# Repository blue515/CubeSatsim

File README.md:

# CubeSatsim
**工作日誌**
https://1drv.ms/w/s!AnrOlf2GZ1a5vx4cTZ3XmwS1Cqu2?e=tUu3Cf

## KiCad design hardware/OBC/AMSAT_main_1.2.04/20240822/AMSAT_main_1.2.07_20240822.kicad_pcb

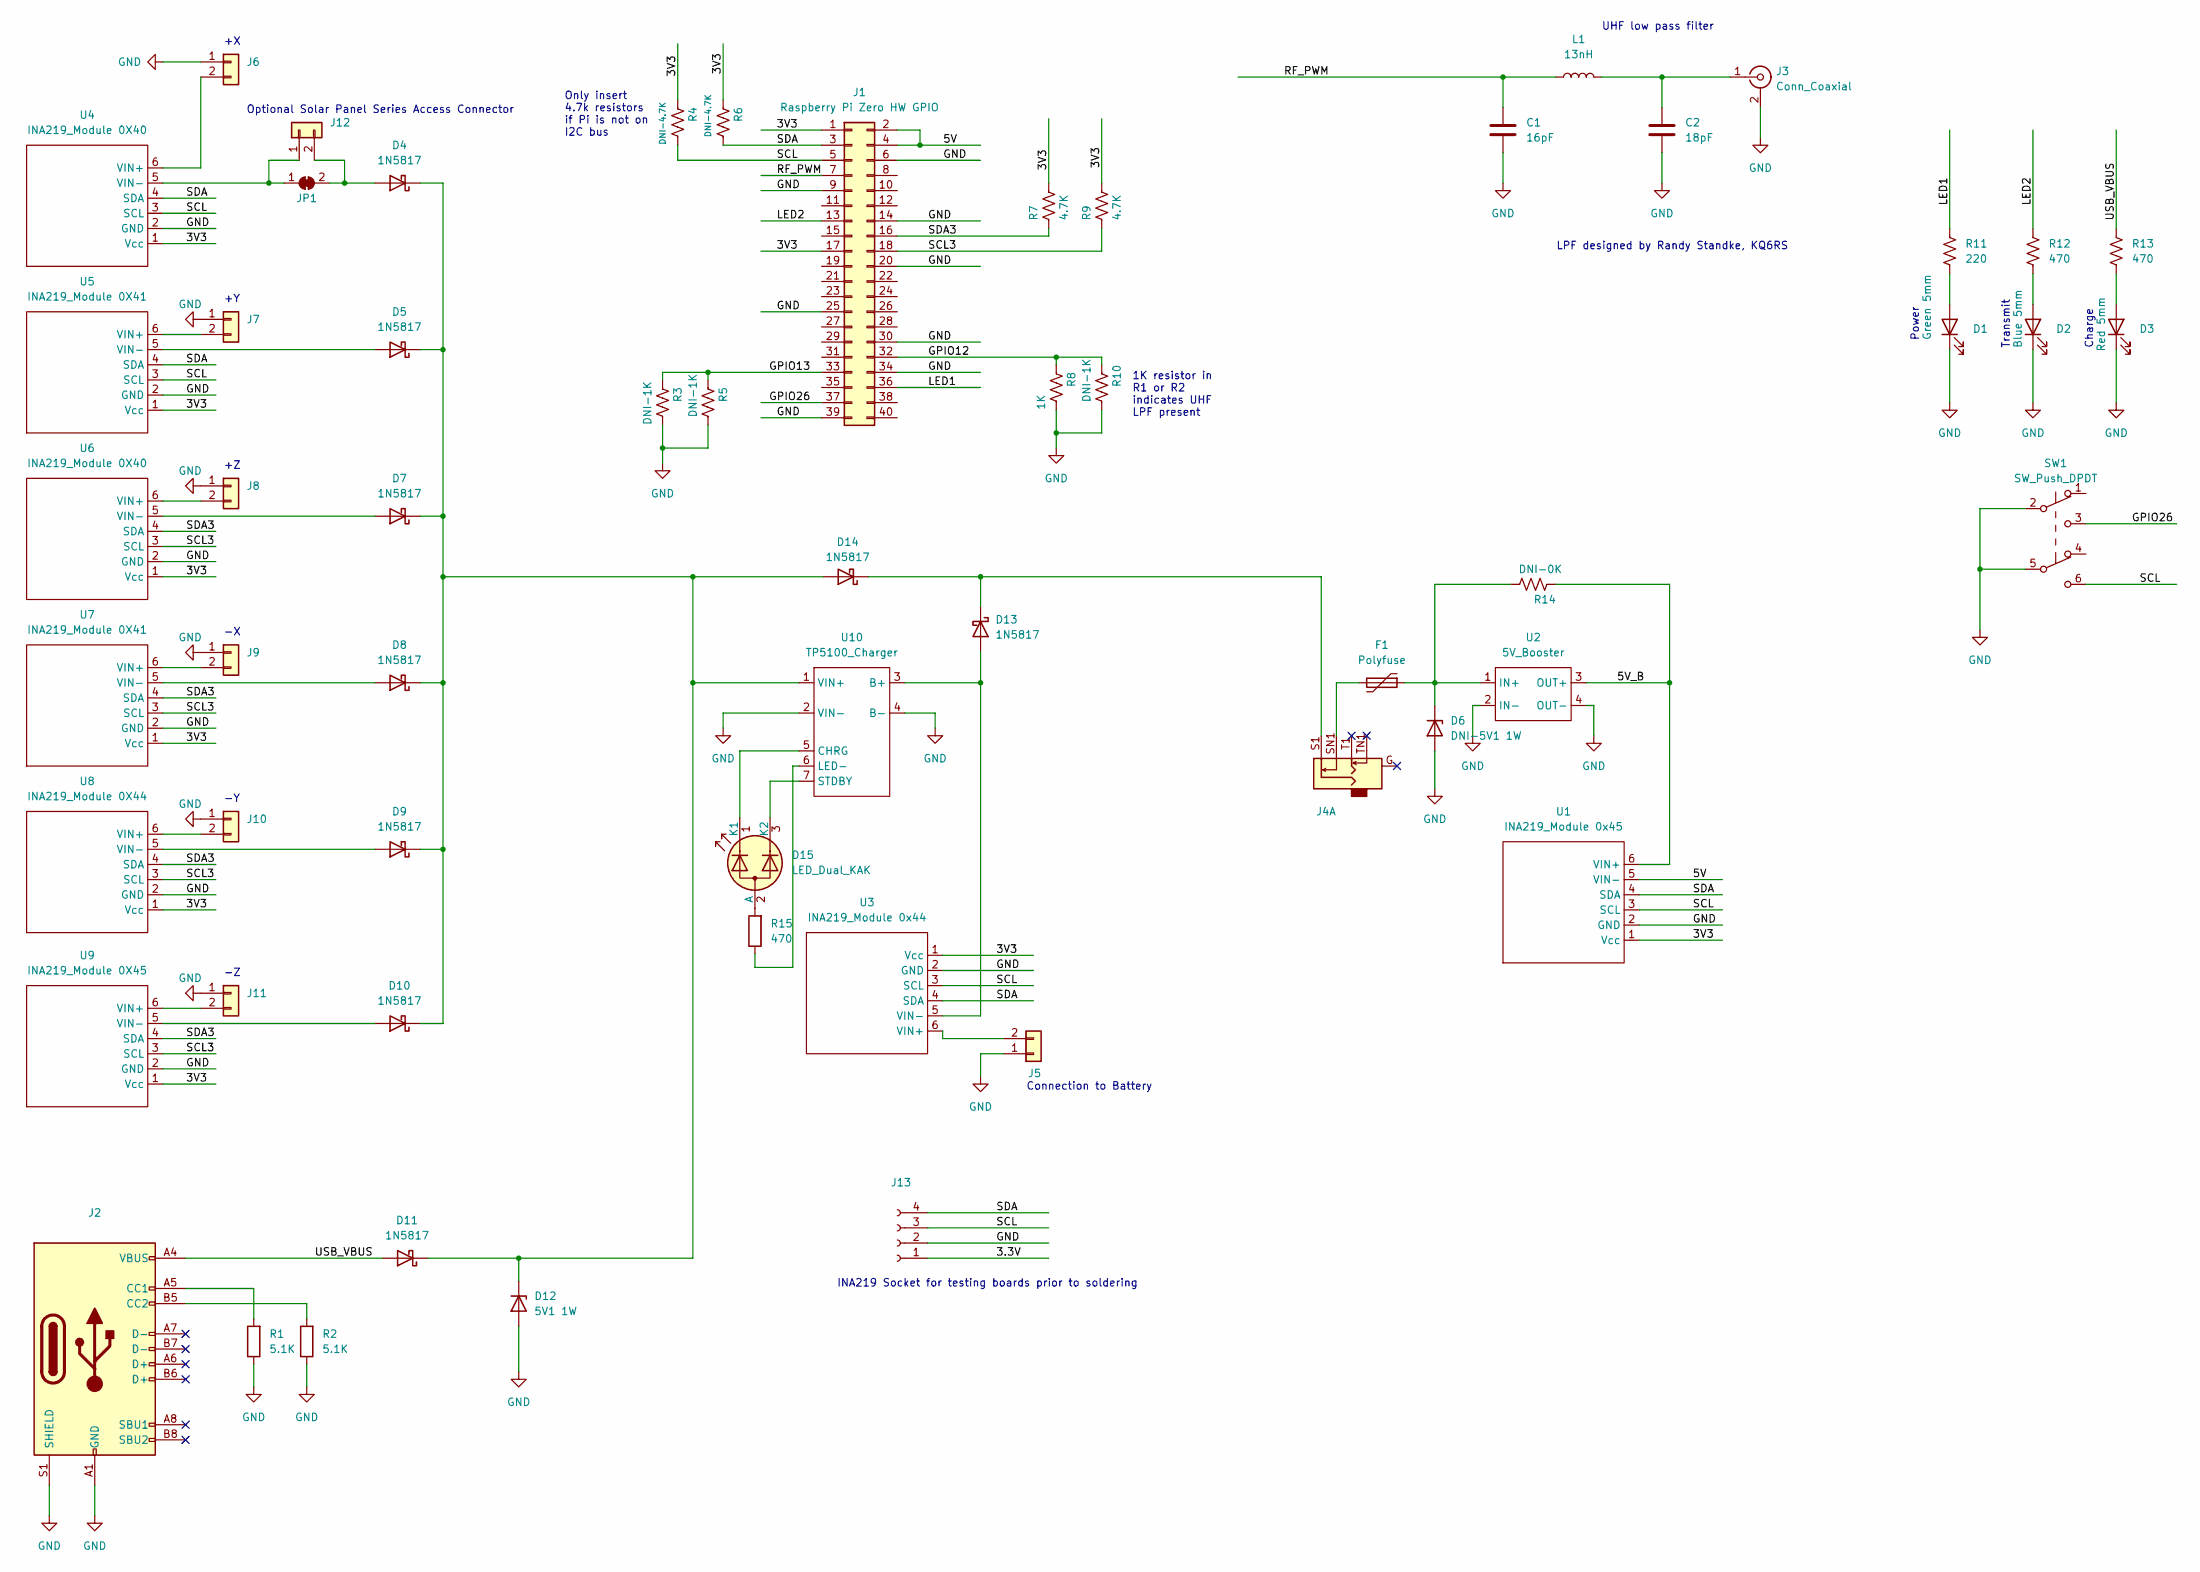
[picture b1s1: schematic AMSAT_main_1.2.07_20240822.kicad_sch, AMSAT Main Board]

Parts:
C1: 16pF; C_0603_1608Metric
C2: 18pF; C_0603_1608Metric
D1: Green 5mm; LED_D5.0mm
D2: Blue 5mm; LED_D5.0mm
D3: Red 5mm; LED_D5.0mm
D4, D5, D7, D8, D9, D10, D11, D13, D14: 1N5817; SS14
D6: DNI-5V1 1W; 1N5817
D12: 5V1 1W; 1N5817
D15: LED_Dual_KAK; LED_D3.0mm-3
F1: Polyfuse; Fuse_1812_4532Metric
J1: Raspberry Pi Zero HW GPIO; PinSocket_2x20_P2.54mm_Vertical
J2: USB_C_Receptacle_USB2.0; USB_C_Receptacle_GCT_USB4105-xx-A_16P_TopMnt_Horizontal
J3: Conn_Coaxial; AMSAT_SMA_Vertical
J4: AudioJack2_Dual_Ground_Switch; Jack_3.5mm_CUI_SJ1-3525N_Horizontal
J5, J6, J7, J8, J9, J10, J11, J12: Conn_01x02; JST_PH_B2B-PH-K_1x02_P2.00mm_Vertical
J13: Conn_01x04_Female; PinHeader_1x04_P2.54mm_Vertical
JP1: SolderJumper_2_Bridged; SolderJumper-2_P1.3mm_Bridged_Pad1.0x1.5mm
L1: 13nH; L_0603_1608Metric
R1, R2: 5.1K; R_0603_1608Metric
R3: DNI-1K; R_Axial_DIN0204_L3.6mm_D1.6mm_P2.54mm_Vertical
R4, R6: DNI-4.7K; R_Axial_DIN0204_L3.6mm_D1.6mm_P2.54mm_Vertical
R5, R10: DNI-1K; R_0603_1608Metric
R7, R9: 4.7K; R_Axial_DIN0204_L3.6mm_D1.6mm_P2.54mm_Vertical
R8: 1K; R_Axial_DIN0204_L3.6mm_D1.6mm_P2.54mm_Vertical
R11: 220; R_Axial_DIN0204_L3.6mm_D1.6mm_P2.54mm_Vertical
R12, R13: 470; R_Axial_DIN0204_L3.6mm_D1.6mm_P2.54mm_Vertical
R14: DNI-0K; R_0805_2012Metric
R15: 470; R_0603_1608Metric
SW1: SW_Push_DPDT; SW_Push_2P2T_Vertical_E-Switch_800UDP8P1A1M6
U1: INA219_Module 0x45; INA219_Small
U2: 5V_Booster; 5V Booster
U3: INA219_Module 0x44; INA219_Small
U4, U6: INA219_Module 0X40; INA219_Small
U5, U7: INA219_Module 0X41; INA219_Small
U8: INA219_Module 0X44; INA219_Small
U9: INA219_Module 0X45; INA219_Small
U10: TP5100_Charger; TP5100 Charger

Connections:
/3.3V: J13.1
/3V3: J1.1, J1.17, R4.1, R6.1, R7.1, R9.1, U1.1 (Vcc), U3.1 (Vcc), U4.1 (Vcc), U5.1 (Vcc), U6.1 (Vcc), U7.1 (Vcc), U8.1 (Vcc), U9.1 (Vcc)
/5V: J1.2, J1.4, U1.5 (VIN-)
/5V_B: R14.1, U1.6 (VIN+), U2.3 (OUT+)
/GPIO12: J1.32, R8.1, R10.1
/GPIO13: J1.33, R3.1, R5.1
/GPIO26: J1.37, SW1.3 (C)
/LED1: J1.36, R11.1
/LED2: J1.13, R12.1
/RF_PWM: C1.1, J1.7, L1.1
/SCL: J1.5, J13.3, R4.2, SW1.6 (C), U1.3 (SCL), U3.3 (SCL), U4.3 (SCL), U5.3 (SCL)
/SCL3: J1.18, R9.2, U6.3 (SCL), U7.3 (SCL), U8.3 (SCL), U9.3 (SCL)
/SDA: J1.3, J13.4, R6.2, U1.4 (SDA), U3.4 (SDA), U4.4 (SDA), U5.4 (SDA)
/SDA3: J1.16, R7.2, U6.4 (SDA), U7.4 (SDA), U8.4 (SDA), U9.4 (SDA)
/USB_VBUS: D11.2 (A), J2.A4 (VBUS), J2.A9 (VBUS), J2.B4 (VBUS), J2.B9 (VBUS), R13.1; also elsewhere on the board
GND: C1.2, C2.2, D1.1 (K), D2.1 (K), D3.1 (K), D6.2 (A), D12.2 (A), J1.6, J1.9, J1.14, J1.20, J1.25, J1.30, J1.34, J1.39, J2.A1 (GND), J2.A12 (GND), J2.B1 (GND), J2.B12 (GND), J2.S1 (SHIELD), J3.2 (Ext), J5.1, J6.1, J7.1, J8.1, J9.1, J10.1, J11.1, J13.2, R1.1, R2.1, R3.2, R5.2, R8.2, R10.2, SW1.2 (B), SW1.5 (B), U1.2 (GND), U2.2 (IN-), U2.4 (OUT-), U3.2 (GND), U4.2 (GND), U5.2 (GND), U6.2 (GND), U7.2 (GND), U8.2 (GND), U9.2 (GND), U10.2 (VIN-), U10.4 (B-); also elsewhere on the board
unnamed: D1.2 (A), R11.2
unnamed: D2.2 (A), R12.2
unnamed: D3.2 (A), R13.2
unnamed: D4.2 (A), J12.2, JP1.2 (B)
unnamed: D5.2 (A), U5.5 (VIN-)
unnamed: D6.1 (K), F1.1, R14.2, U2.1 (IN+)
unnamed: D7.2 (A), U6.5 (VIN-)
unnamed: D8.2 (A), U7.5 (VIN-)
unnamed: D9.2 (A), U8.5 (VIN-)
unnamed: D10.2 (A), U9.5 (VIN-)
unnamed: D4.1 (K), D5.1 (K), D7.1 (K), D8.1 (K), D9.1 (K), D10.1 (K), D11.1 (K), D12.1 (K), D14.2 (A), U10.1 (VIN+)
unnamed: D13.2 (A), U3.5 (VIN-), U10.3 (B+)
unnamed: D13.1 (K), D14.1 (K), J4.S1
unnamed: D15.2 (A), R15.2
unnamed: D15.1 (K1), U10.5 (CHRG)
unnamed: D15.3 (K2), U10.7 (STDBY)
unnamed: F1.2, J4.SN1
unnamed: J2.A5 (CC1), R1.2
unnamed: J2.B5 (CC2), R2.2
unnamed: C2.1, J3.1 (In), L1.2
unnamed: J5.2, U3.6 (VIN+)
unnamed: J6.2, U4.6 (VIN+)
unnamed: J7.2, U5.6 (VIN+)
unnamed: J8.2, U6.6 (VIN+)
unnamed: J9.2, U7.6 (VIN+)
unnamed: J10.2, U8.6 (VIN+)
unnamed: J11.2, U9.6 (VIN+)
unnamed: J12.1, JP1.1 (A), U4.5 (VIN-)
unnamed: R15.1, U10.6 (LED-)

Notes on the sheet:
Power
LPF designed by Randy Standke, KQ6RS
UHF low pass filter
Optional Solar Panel Series Access Connector
Transmit
INA219 Socket for testing boards prior to soldering
1K resistor in R1 or R2 indicates UHF LPF present
Only insert 4.7k resistors if Pi is not on I2C bus
Charge
Connection to Battery

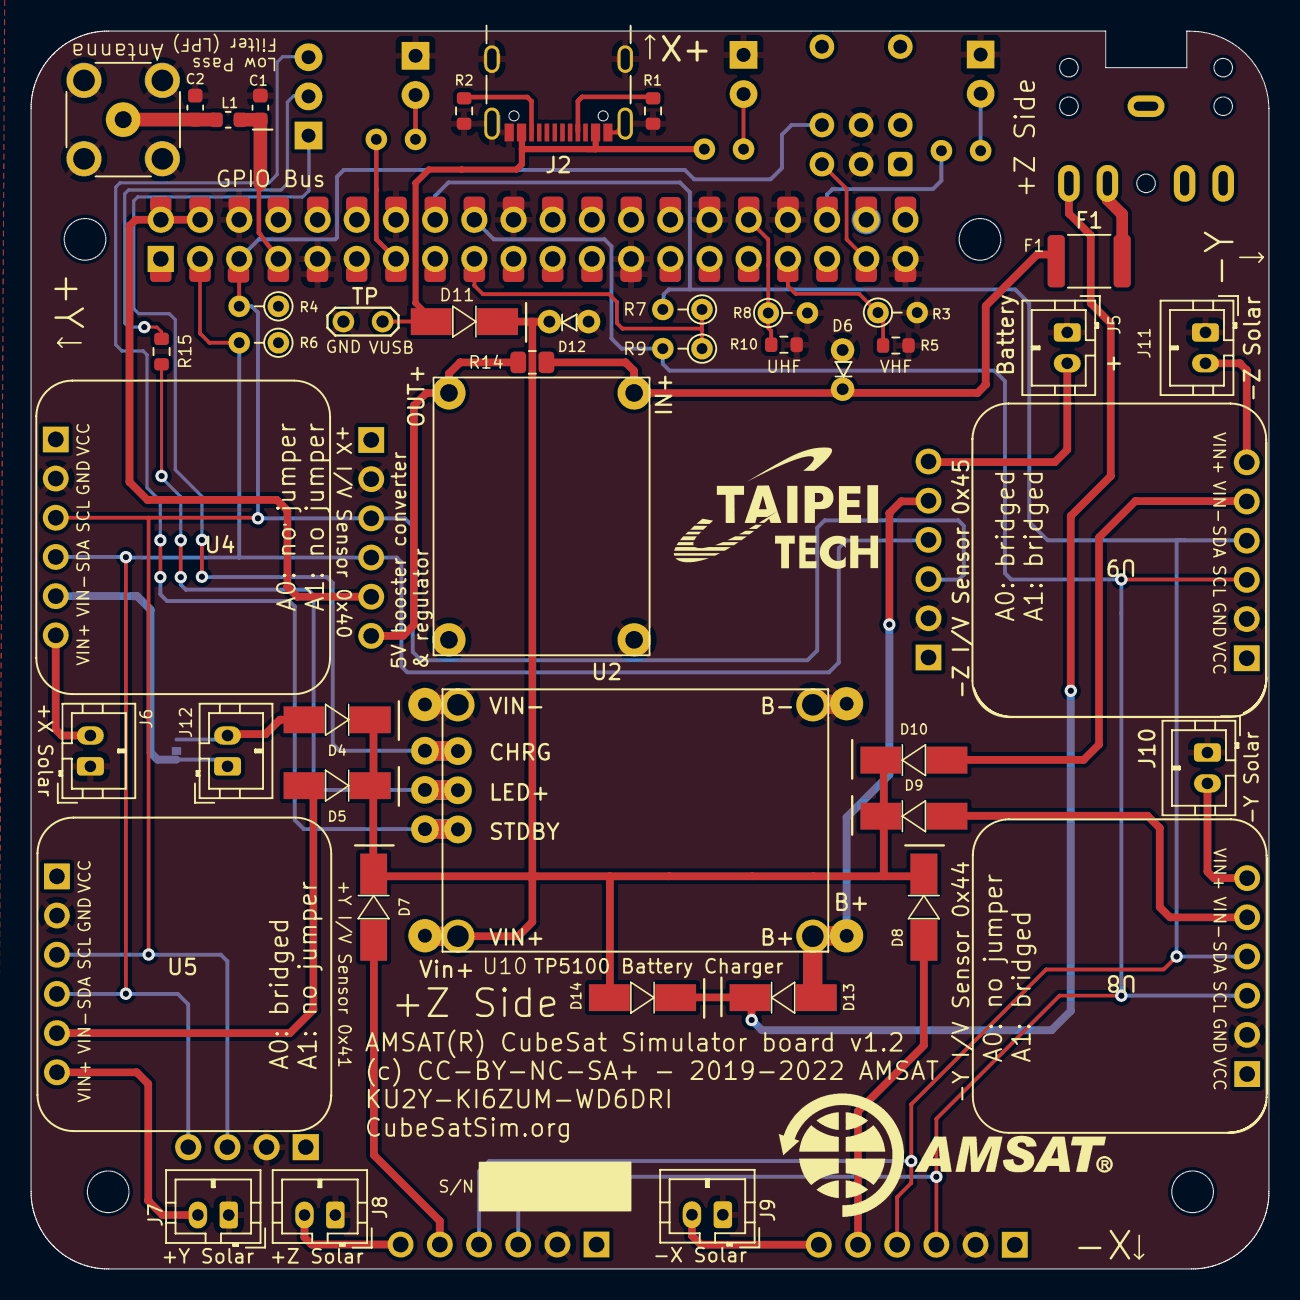
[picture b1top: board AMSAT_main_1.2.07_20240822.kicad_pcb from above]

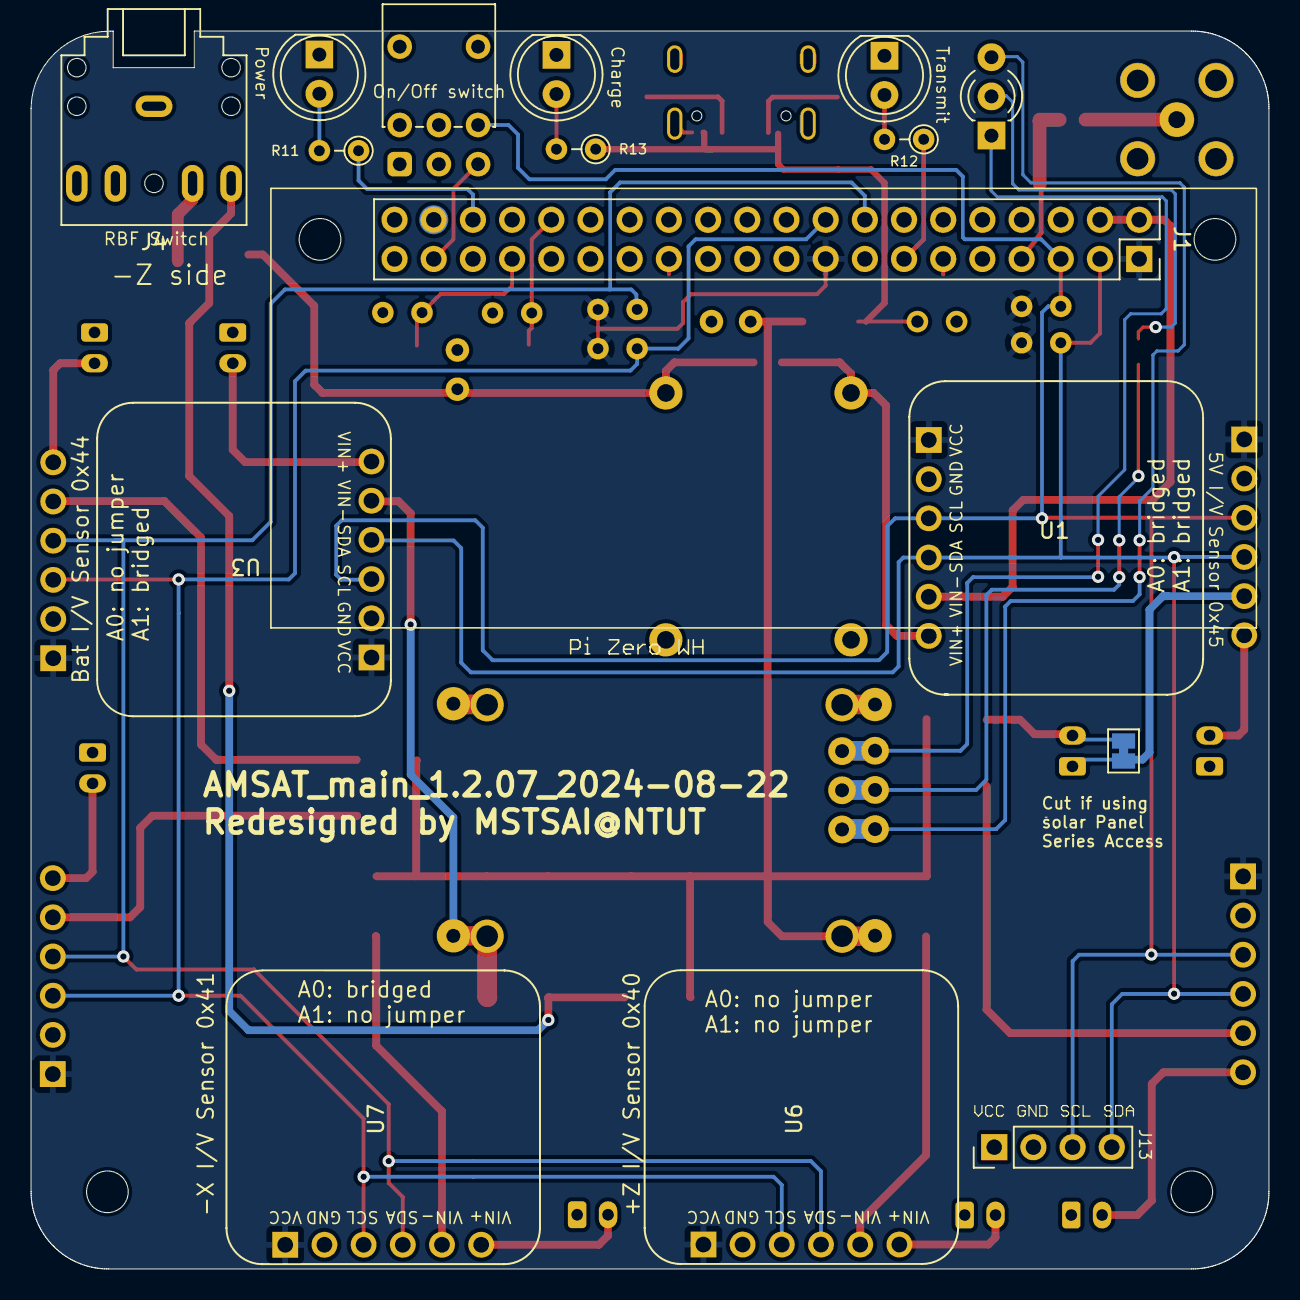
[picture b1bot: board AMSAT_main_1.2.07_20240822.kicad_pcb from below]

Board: 2 copper layers, 80.2 x 80.2 mm, 60 parts (16 on the bottom side), 43 nets.

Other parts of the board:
TP: TestPoint_2Pads_Pitch2.54mm_Drill0.8mm

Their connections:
/USB_VBUS: TP.1; also elsewhere on the board
GND: TP.2; also elsewhere on the board

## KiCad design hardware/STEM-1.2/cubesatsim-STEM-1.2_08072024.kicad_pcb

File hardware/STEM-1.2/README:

This directory contains KiCAD files for STEM-1.2 which uses BlackPill as the main processor.

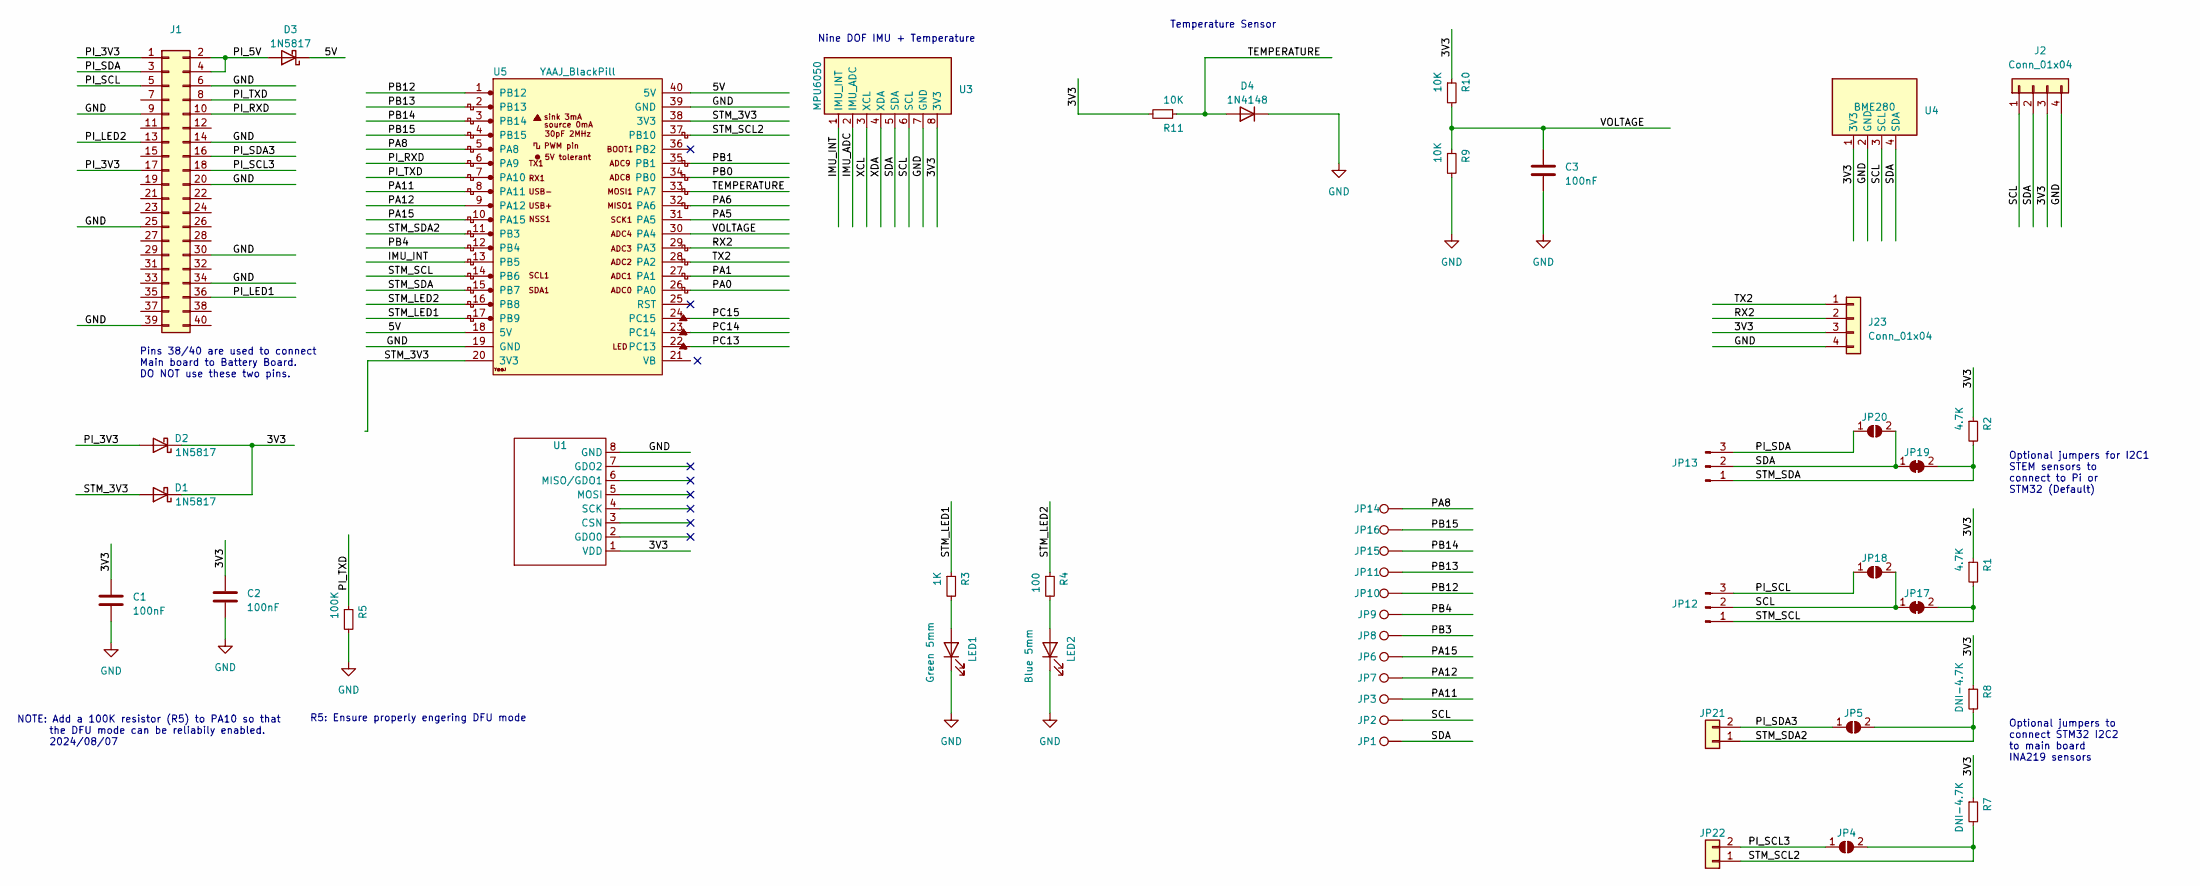
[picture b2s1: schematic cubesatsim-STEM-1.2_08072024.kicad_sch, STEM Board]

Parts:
C1, C2, C3: 100nF; AMSAT_C_TH_5.08
D1, D2, D3: 1N5817; 1N5817_TH_100mil
D4: 1N4148; 1N5817_TH_100mil
J1: Conn_02x20_Odd_Even; PinHeader_2x20_P2.54mm_Vertical
J2, J23: Conn_01x04; PinHeader_1x04_P2.54mm_Vertical
JP1, JP2, JP3, JP6, JP7, JP8, JP9, JP10, JP11, JP14, JP15, JP16: TestPoint; Test_Point_Vertical_S
JP4, JP5, JP18, JP20: SolderJumper_2_Open; SolderJumper-2_P1.3mm_Open_Pad1.0x1.5mm
JP12, JP13: Conn_01x03_Pin; PinHeader_1x03_P2.54mm_Vertical
JP17, JP19: SolderJumper_2_Bridged; SolderJumper-2_P1.3mm_Bridged_Pad1.0x1.5mm
JP21, JP22: Conn_01x02; PinHeader_1x02_P2.54mm_Vertical
LED1: Green 5mm; LED_D3.0mm
LED2: Blue 5mm; LED_D3.0mm
R1, R2: 4.7K; R_TH_V_2.54
R3: 1K; R_TH_V_2.54
R4: 100; R_TH_V_2.54
R5: 100K; R_TH_V_2.54
R7, R8: DNI-4.7K; R_TH_V_2.54
R9, R10, R11: 10K; R_TH_V_2.54
U1: CC1101_127
U3: MPU6050; MPU6050_IMU_Module
U4: BME280; BME280_Module
U5: YAAJ_BlackPill; YAAJ_BlackPill_2

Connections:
/3V3: C1.1, C2.1, D1.1 (K), D2.1 (K), J2.3, J23.3, R1.1, R2.1, R7.1, R8.1, R10.1, R11.2, U1.1 (VDD), U3.8 (3V3), U4.1 (3V3)
/5V: D3.1 (K), U5.18 (5V), U5.40 (5V)
/IMU_ADC: U3.2 (IMU_ADC)
/IMU_INT: U3.1 (IMU_INT), U5.13 (PB5)
/PA0: U5.26 (PA0)
/PA1: U5.27 (PA1)
/PA5: U5.31 (PA5)
/PA6: U5.32 (PA6)
/PA8: JP14.1, U5.5 (PA8)
/PA11: JP3.1, U5.8 (PA11)
/PA12: JP7.1, U5.9 (PA12)
/PA15: JP6.1, U5.10 (PA15)
/PB0: U5.34 (PB0)
/PB1: U5.35 (PB1)
/PB3: JP8.1
/PB4: JP9.1, U5.12 (PB4)
/PB12: JP10.1, U5.1 (PB12)
/PB13: JP11.1, U5.2 (PB13)
/PB14: JP15.1, U5.3 (PB14)
/PB15: JP16.1, U5.4 (PB15)
/PC13: U5.22 (PC13)
/PC14: U5.23 (PC14)
/PC15: U5.24 (PC15)
/PI_3V3: D2.2 (A), J1.1, J1.17
/PI_5V: D3.2 (A), J1.2, J1.4
/PI_LED1: J1.36
/PI_LED2: J1.13
/PI_RXD: J1.10, U5.6 (PA9)
/PI_SCL: J1.5, JP12.3, JP18.1 (A)
/PI_SCL3: J1.18, JP4.1 (A), JP22.2
/PI_SDA: J1.3, JP13.3, JP20.1 (A)
/PI_SDA3: J1.16, JP5.1 (A), JP21.2
/PI_TXD: J1.8, R5.1, U5.7 (PA10)
/RX2: J23.2, U5.29 (PA3)
/SCL: J2.1, JP2.1, JP12.2, JP17.1 (A), JP18.2 (B), U3.6 (SCL), U4.3 (SCL)
/SDA: J2.2, JP1.1, JP13.2, JP19.1 (A), JP20.2 (B), U3.5 (SDA), U4.4 (SDA)
/STM_3V3: D1.2 (A), U5.20 (3V3), U5.38 (3V3)
/STM_LED1: R3.1, U5.17 (PB9)
/STM_LED2: R4.1, U5.16 (PB8)
/STM_SCL: JP12.1, JP17.2 (B), R1.2, U5.14 (PB6)
/STM_SCL2: JP4.2 (B), JP22.1, R7.2, U5.37 (PB10)
/STM_SDA: JP13.1, JP19.2 (B), R2.2, U5.15 (PB7)
/STM_SDA2: JP5.2 (B), JP21.1, R8.2, U5.11 (PB3)
/TEMPERATURE: D4.2 (A), R11.1, U5.33 (PA7)
/TX2: J23.1, U5.28 (PA2)
/VOLTAGE: C3.2, R9.1, R10.2, U5.30 (PA4)
/XCL: U3.3 (XCL)
/XDA: U3.4 (XDA)
GND: C1.2, C2.2, C3.1, D4.1 (K), J1.6, J1.9, J1.14, J1.20, J1.25, J1.30, J1.34, J1.39, J2.4, J23.4, LED1.1 (K), LED2.1 (K), R5.2, R9.2, U1.8 (GND), U3.7 (GND), U4.2 (GND), U5.19 (GND), U5.39 (GND)
unnamed: LED1.2 (A), R3.2
unnamed: LED2.2 (A), R4.2

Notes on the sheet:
Temperature Sensor
Pins 38/40 are used to connect Main board to Battery Board. DO NOT use these two pins.
Optional jumpers to connect STM32 I2C2 to main board INA219 sensors
Optional jumpers for I2C1 STEM sensors to connect to Pi or STM32 (Default)
R5: Ensure properly engering DFU mode
NOTE: Add a 100K resistor (R5) to PA10 so that the DFU mode can be reliabily enabled. 2024/08/07
Nine DOF IMU + Temperature

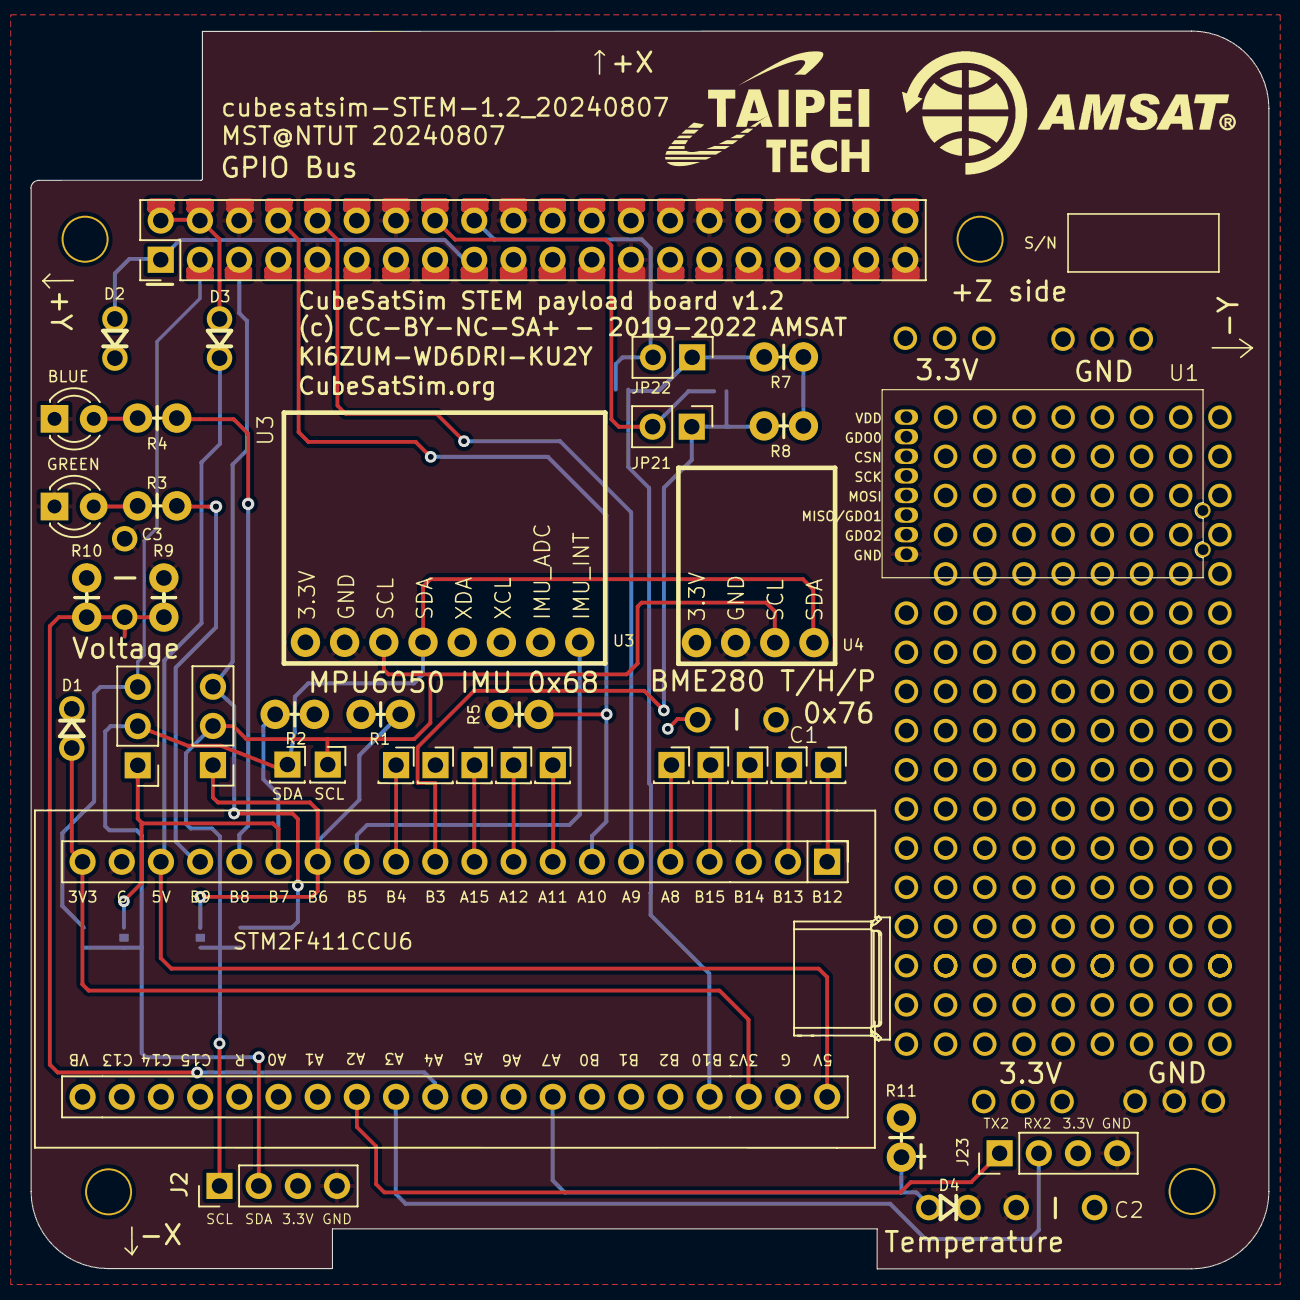
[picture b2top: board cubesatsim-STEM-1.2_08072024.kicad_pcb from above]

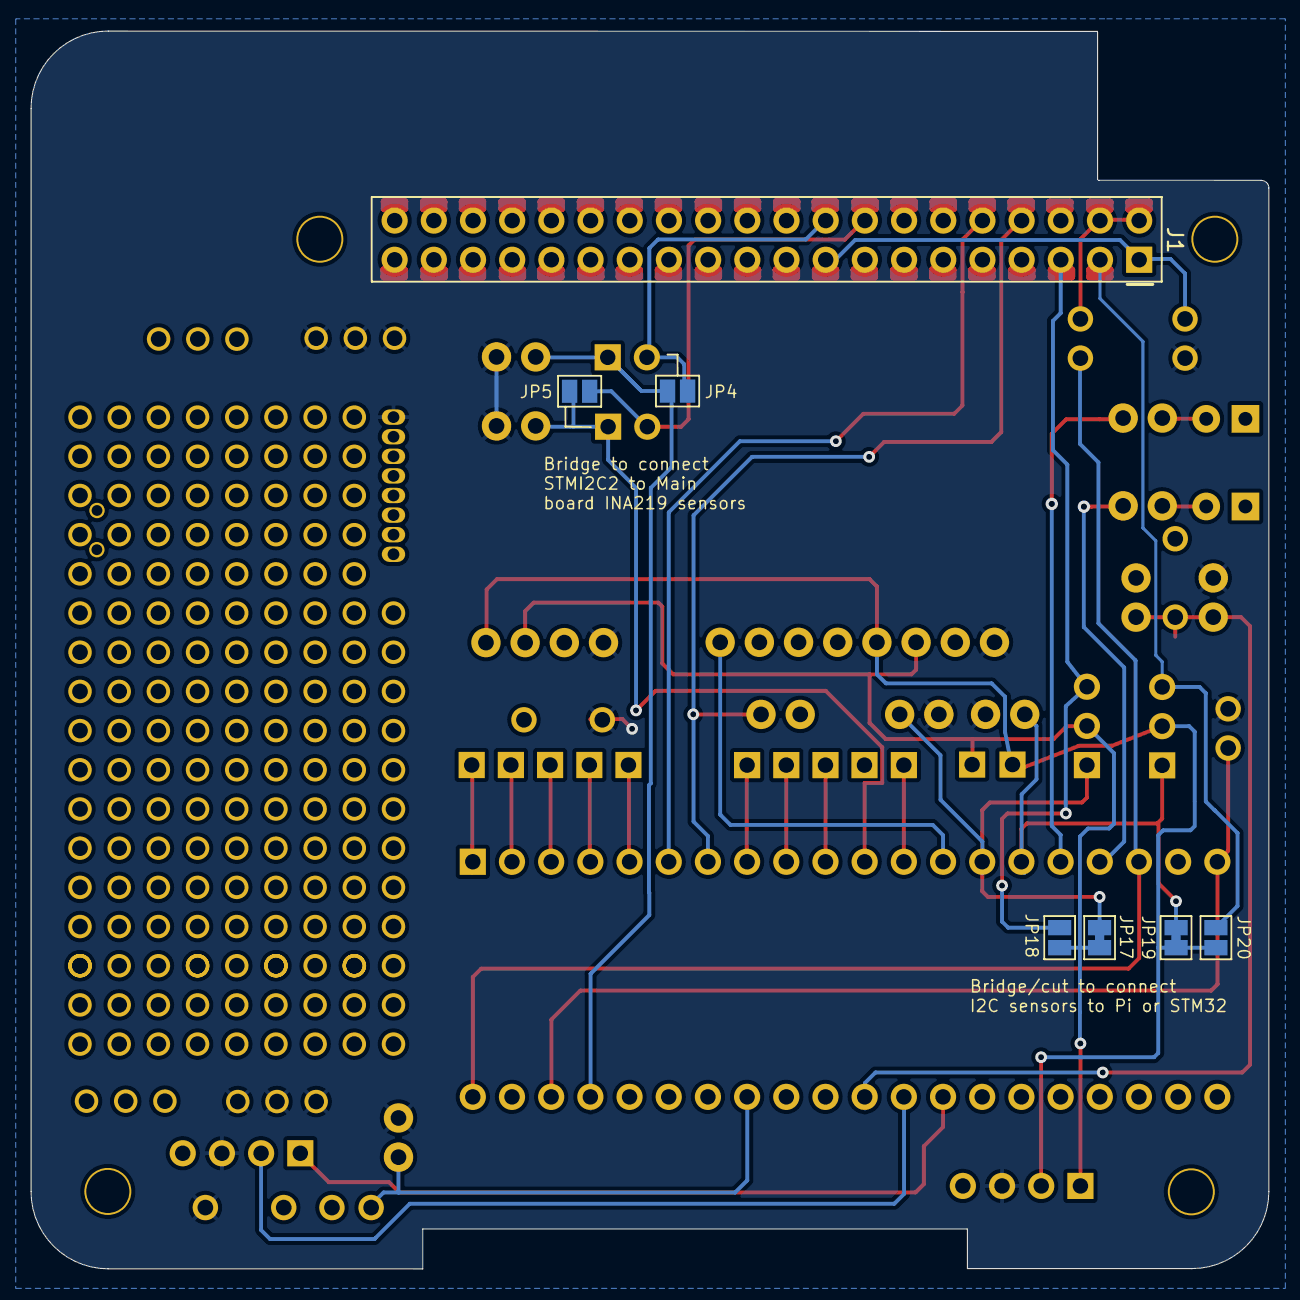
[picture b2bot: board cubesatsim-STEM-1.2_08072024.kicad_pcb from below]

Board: 2 copper layers, 80.2 x 80.2 mm, 48 parts (6 on the bottom side), 35 nets.

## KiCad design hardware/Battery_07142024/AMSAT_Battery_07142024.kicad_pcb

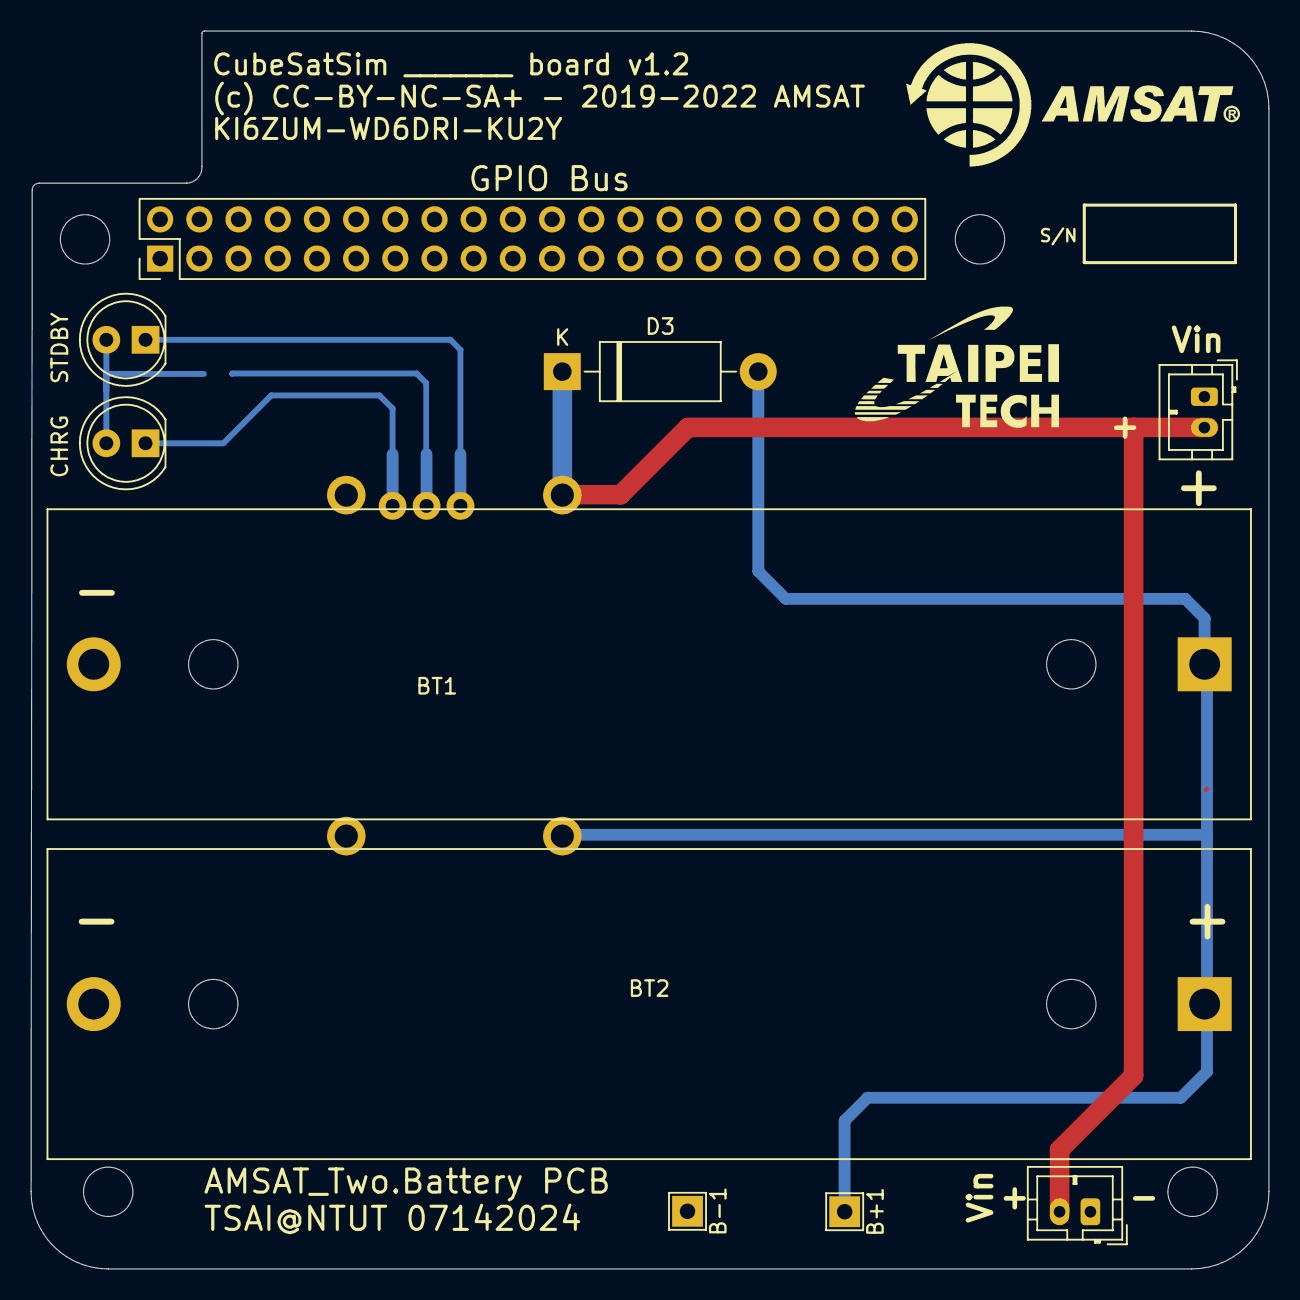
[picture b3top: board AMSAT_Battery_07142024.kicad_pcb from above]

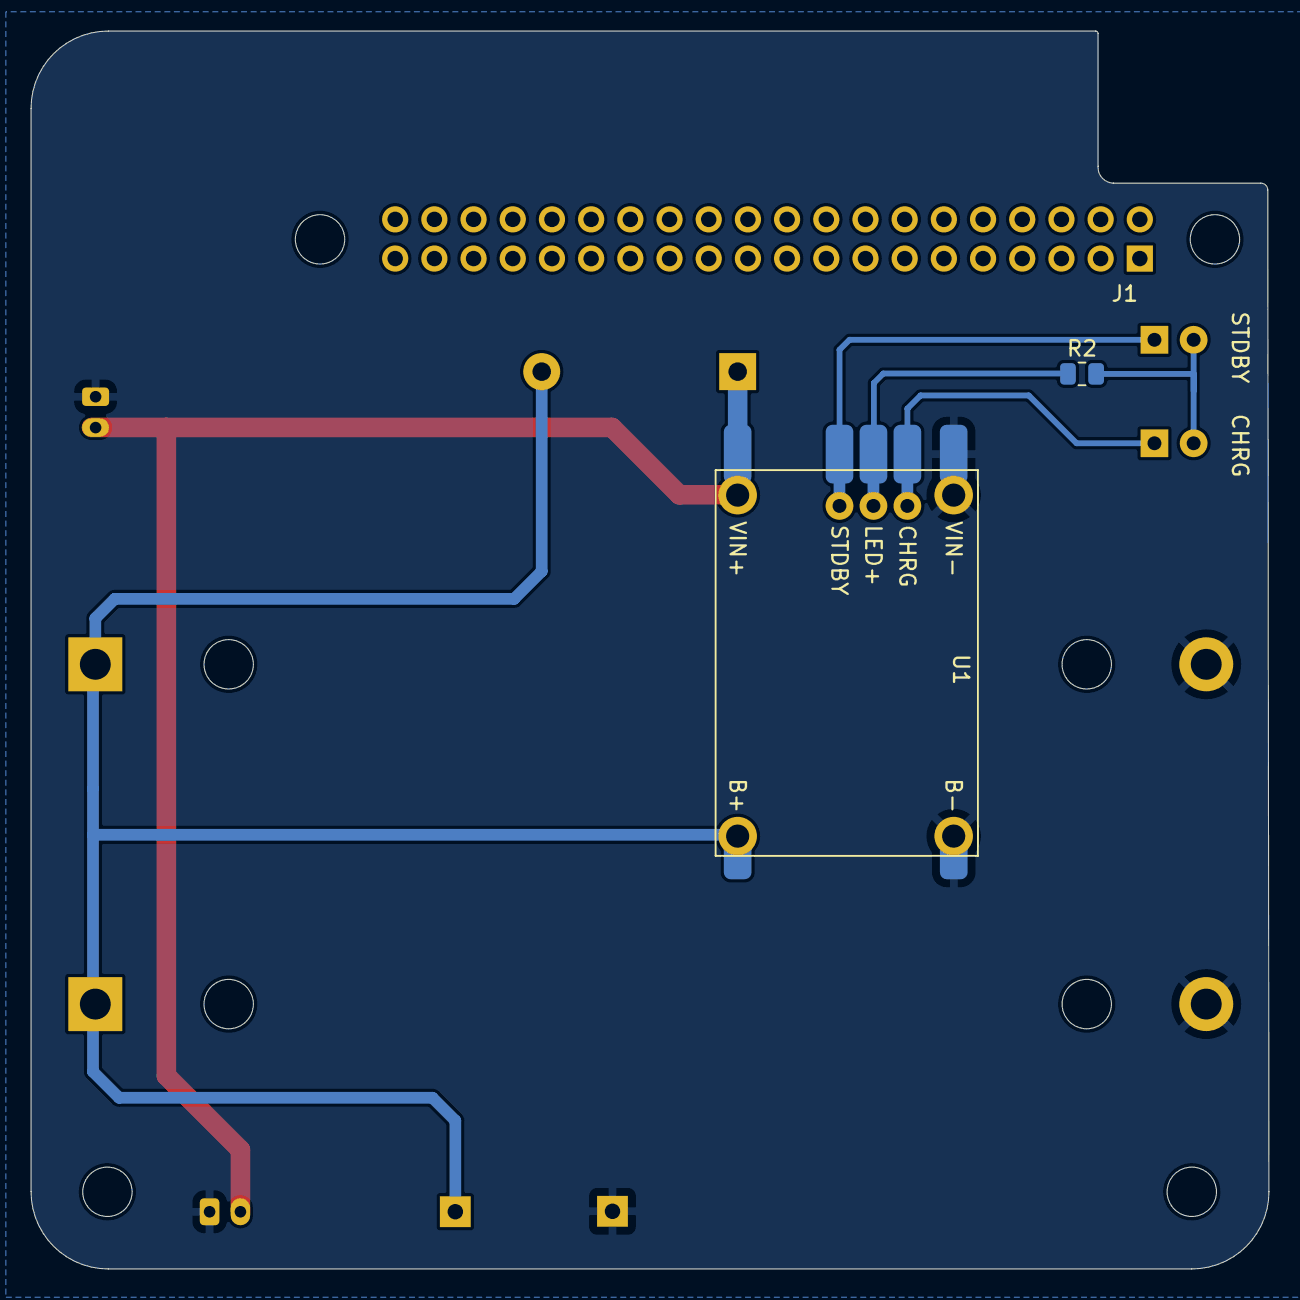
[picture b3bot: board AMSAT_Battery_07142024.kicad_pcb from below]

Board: 2 copper layers, 80.2 x 80.2 mm, 12 parts (2 on the bottom side), 7 nets.

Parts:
B+1: TestPoint; TestPoint_THTPad_2.0x2.0mm_Drill1.0mm
B-1: TestPoint; TestPoint_THTPad_2.0x2.0mm_Drill1.0mm
BT1, BT2: Battery_Cell; BatteryHolder_MPD_BH-18650-PC2
D1, D2: LED; LED_D5.0mm
D3: 1N5817; D_DO-15_P12.70mm_Horizontal
J1: Conn_01x02; JST_PH_B2B-PH-K_1x02_P2.00mm_Vertical
J1#2: Conn_02x20_Odd_Even; PinHeader_2x20_P2.54mm_Vertical
J10: Battery; JST_PH_B2B-PH-K_1x02_P2.00mm_Vertical
R2: 1K; R_0805_2012Metric
U1: TP5100_Charger; TP5100 Charger

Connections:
GND: B-1.1, BT1.2 (-), BT2.2 (-), J1.1, J10.1, U1.2 (VIN-), U1.4 (B-)
unnamed: B+1.1, BT1.1 (+), BT2.1 (+), D3.2 (A), U1.3 (B+)
unnamed: D1.2 (A), D2.2 (A), R2.2
unnamed: D1.1 (K), U1.7 (STDBY)
unnamed: D2.1 (K), U1.5 (CHRG)
unnamed: D3.1 (K), J1.2, J10.2, U1.1 (VIN+)
unnamed: R2.1, U1.6 (LED+)

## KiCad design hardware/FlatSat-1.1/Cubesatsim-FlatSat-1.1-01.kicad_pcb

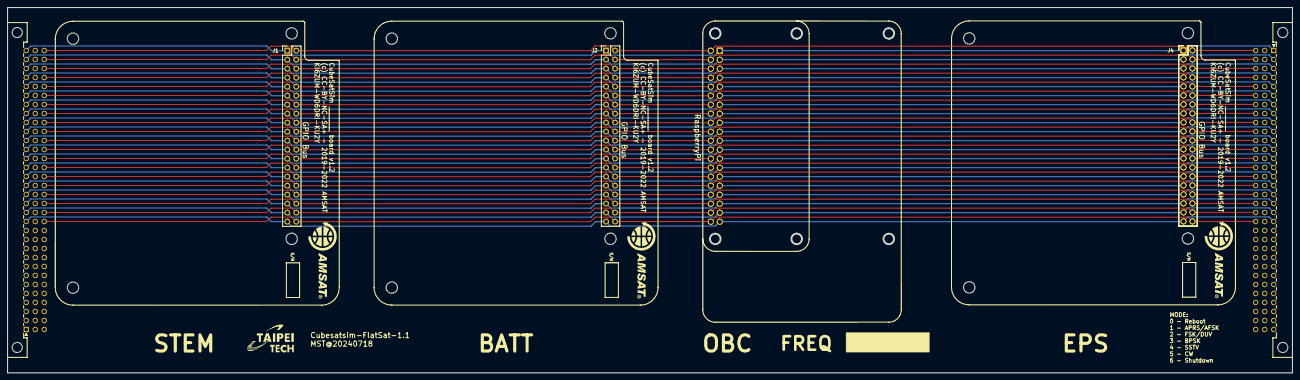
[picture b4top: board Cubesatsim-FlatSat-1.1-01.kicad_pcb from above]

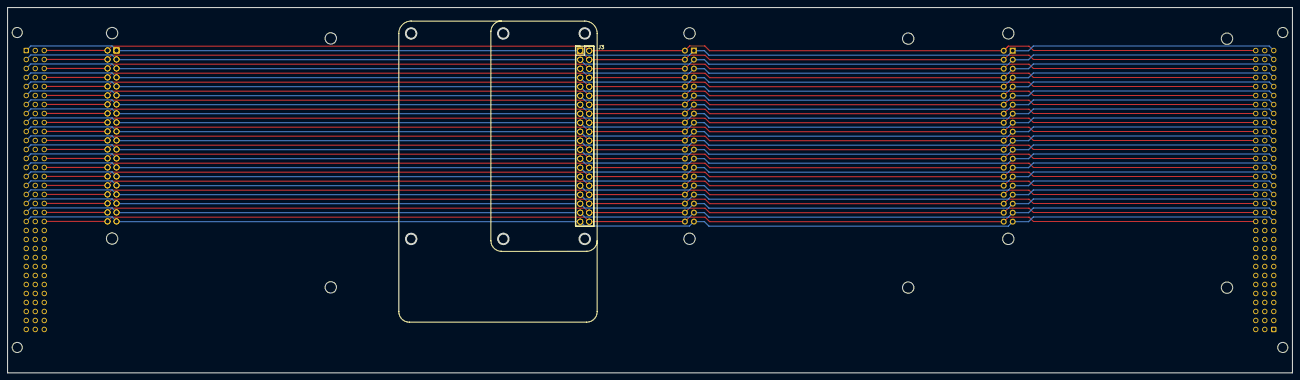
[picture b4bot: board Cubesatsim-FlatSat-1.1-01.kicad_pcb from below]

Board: 2 copper layers, 362.7 x 103.1 mm, 6 parts (2 on the bottom side), 31 nets.

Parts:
J1, J1#2, J2, J3, J4: Conn_02x20_Odd_Even; PinHeader_2x20_P2.54mm_Vertical
RP?: Raspberry_Pi/Zero; raspberrypi_3_zero

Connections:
/3V3: J1.1, J1.17, J2.1, J2.17, J3.1, J3.17, J4.1, J4.17
/5V: J1.2, J1.4, J2.2, J2.4, J3.2, J3.4, J4.2, J4.4
/GND: J1.6, J1.9, J1.14, J1.20, J1.25, J1.30, J1.34, J1.39, J2.6, J2.9, J2.14, J2.20, J2.25, J2.30, J2.34, J2.39, J3.6, J3.9, J3.14, J3.20, J3.25, J3.30, J3.34, J3.39, J4.6, J4.9, J4.14, J4.20, J4.25, J4.30, J4.34, J4.39
/GPIO2: J1.3, J2.3, J3.3, J4.3
/GPIO3: J1.5, J2.5, J3.5, J4.5
/GPIO4: J1.7, J2.7, J3.7, J4.7
/GPIO5: J1.29, J2.29, J3.29, J4.29
/GPIO6: J1.31, J2.31, J3.31, J4.31
/GPIO7: J1.26, J2.26, J3.26, J4.26
/GPIO8: J1.24, J2.24, J3.24, J4.24
/GPIO9: J1.21, J2.21, J3.21, J4.21
/GPIO10: J1.19, J2.19, J3.19, J4.19
/GPIO11: J1.23, J2.23, J3.23, J4.23
/GPIO12: J1.32, J2.32, J3.32, J4.32
/GPIO13: J1.33, J2.33, J3.33, J4.33
/GPIO16: J1.36, J2.36, J3.36, J4.36
/GPIO17: J1.11, J2.11, J3.11, J4.11
/GPIO18: J1.12, J2.12, J3.12, J4.12
/GPIO19: J1.35, J2.35, J3.35, J4.35
/GPIO20: J1.38, J2.38, J3.38, J4.38
/GPIO21: J1.40, J2.40, J3.40, J4.40
/GPIO22: J1.15, J2.15, J3.15, J4.15
/GPIO23: J1.16, J2.16, J3.16, J4.16
/GPIO24: J1.18, J2.18, J3.18, J4.18
/GPIO25: J1.22, J2.22, J3.22, J4.22
/GPIO26: J1.37, J2.37, J3.37, J4.37
/GPIO27: J1.13, J2.13, J3.13, J4.13
/SDA: J1#2.3, RP?.3
/UART0_RX: J1.10, J2.10, J3.10, J4.10
/UART0_TX: J1.8, J2.8, J3.8, J4.8
unnamed: J1#2.1, RP?.1

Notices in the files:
hardware/Battery_07142024/AMSAT_Battery_07142024.kicad_pcb:
(c) CC-BY-NC-SA+ - 2019-2022 AMSAT
